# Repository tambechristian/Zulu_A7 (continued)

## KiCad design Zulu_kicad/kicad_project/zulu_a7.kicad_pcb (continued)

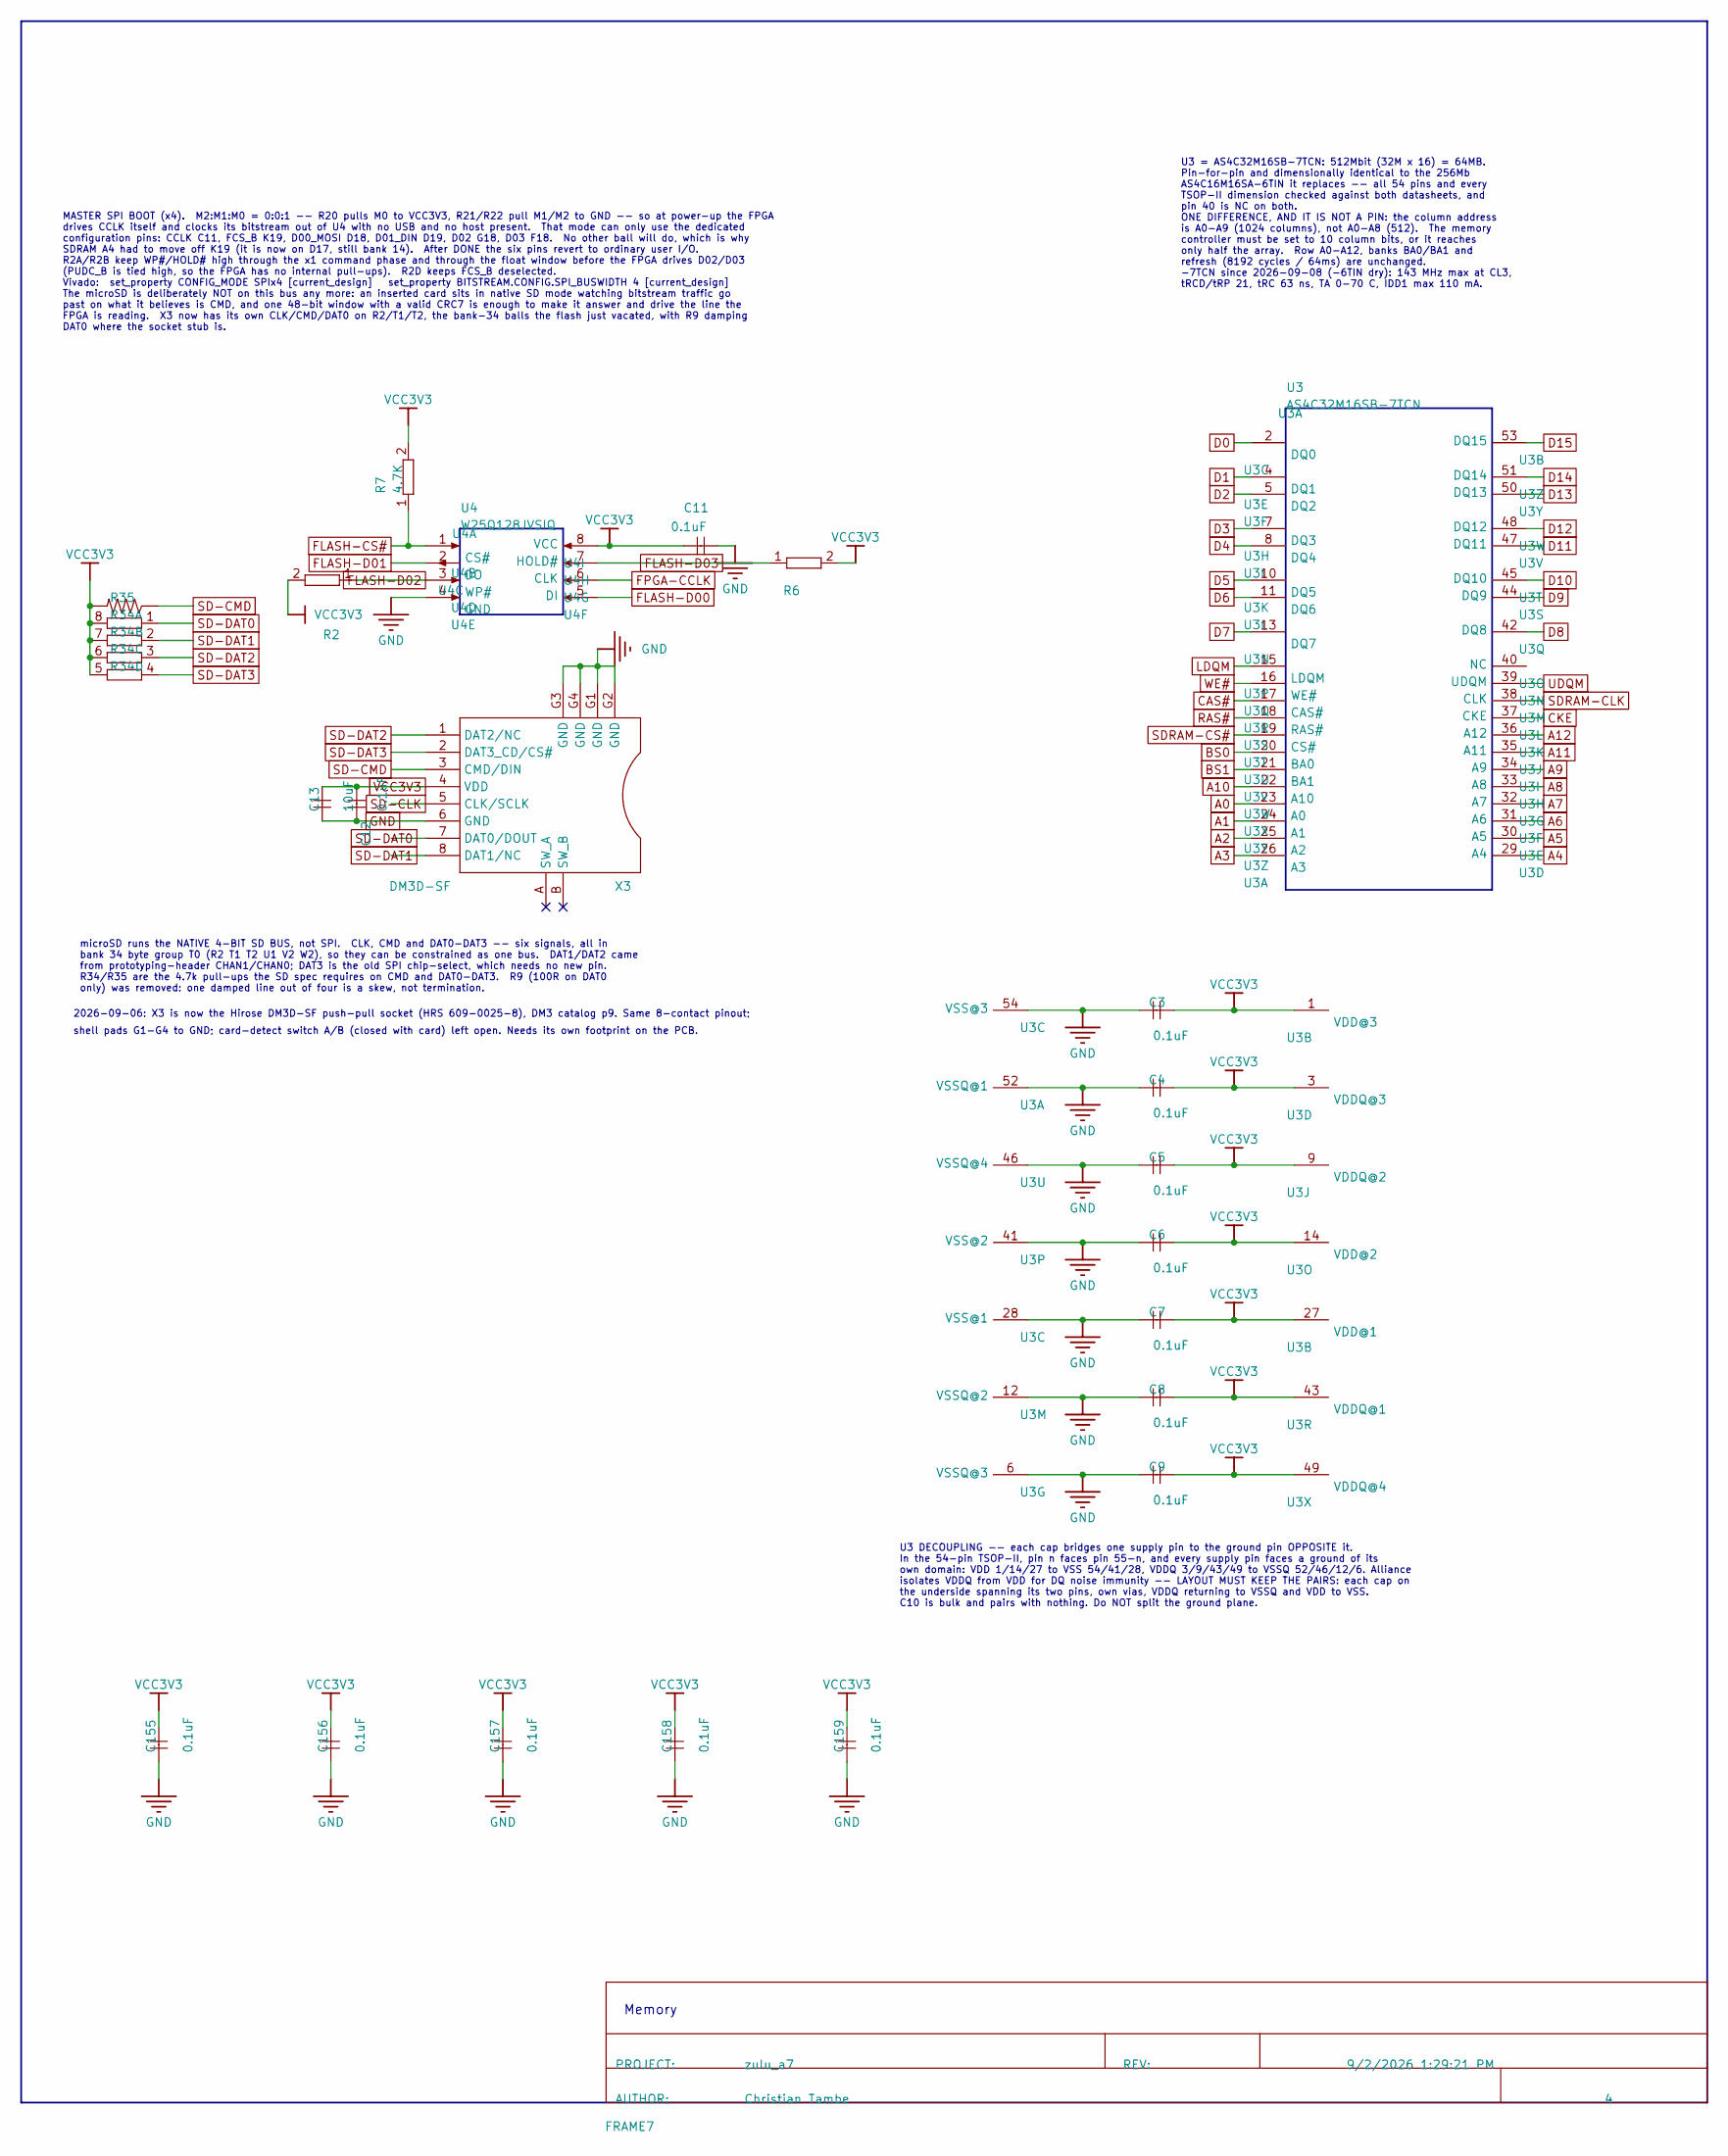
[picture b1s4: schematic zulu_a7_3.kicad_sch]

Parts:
C3, C4, C5, C6, C7, C8, C9, C11, C12: 0.1uF; C0402
C13: 10uF; C0603
C155, C156, C157, C158, C159: 0.1uF; C0201
FRAME7: DOCFIELD
R2, R6, R7: 4.7K; R0201
R34: 4.7K; 742C083; MOUSER# 774-742C083???JP; DIGIKEY# 742C083???JPCT-ND
R35: 4.7K; R0402
U3: AS4C32M16SB-7TCN; TSOPII-54
U4: W25Q128JVSIQ; SOIC-8_208MIL; PART U4; DIGIKEY# W25Q128JVSIQ-ND
X3: DM3D-SF; MOUSER# MOUSER#

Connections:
A0: U3.23; also elsewhere on the board
A1: U3.24; also elsewhere on the board
A2: U3.25; also elsewhere on the board
A3: U3.26; also elsewhere on the board
A4: U3.29; also elsewhere on the board
A5: U3.30; also elsewhere on the board
A6: U3.31; also elsewhere on the board
A7: U3.32; also elsewhere on the board
A8: U3.33; also elsewhere on the board
A9: U3.34; also elsewhere on the board
A10: U3.22; also elsewhere on the board
A11: U3.35; also elsewhere on the board
A12: U3.36; also elsewhere on the board
BS0: U3.20; also elsewhere on the board
BS1: U3.21; also elsewhere on the board
CAS#: U3.17; also elsewhere on the board
CKE: U3.37; also elsewhere on the board
D0: U3.2; also elsewhere on the board
D1: U3.4; also elsewhere on the board
D2: U3.5; also elsewhere on the board
D3: U3.7; also elsewhere on the board
D4: U3.8; also elsewhere on the board
D5: U3.10; also elsewhere on the board
D6: U3.11; also elsewhere on the board
D7: U3.13; also elsewhere on the board
D8: U3.42; also elsewhere on the board
D9: U3.44; also elsewhere on the board
D10: U3.45; also elsewhere on the board
D11: U3.47; also elsewhere on the board
D12: U3.48; also elsewhere on the board
D13: U3.50; also elsewhere on the board
D14: U3.51; also elsewhere on the board
D15: U3.53; also elsewhere on the board
FLASH-CS#: R7.1, U4.1; also elsewhere on the board
FLASH-D00: U4.5; also elsewhere on the board
FLASH-D01: U4.2; also elsewhere on the board
FLASH-D02: R2.1, U4.3; also elsewhere on the board
FLASH-D03: R6.1, U4.7; also elsewhere on the board
FPGA-CCLK: U4.6; also elsewhere on the board
GND: C3.1, C4.1, C5.1, C6.1, C7.1, C8.1, C9.1, C11.1, C12.1, C13.1, C155.1, C156.1, C157.1, C158.1, C159.1, U3.6, U3.12, U3.28, U3.41, U3.46, U3.52, U3.54, U4.4, X3.6 (GND), X3.G1 (GND), X3.G2 (GND), X3.G3 (GND), X3.G4 (GND); also elsewhere on the board
LDQM: U3.15; also elsewhere on the board
RAS#: U3.18; also elsewhere on the board
SD-CLK: X3.5 (CLK/SCLK); also elsewhere on the board
SD-CMD: R35.1, X3.3 (CMD/DIN); also elsewhere on the board
SD-DAT0: R34.1, X3.7 (DAT0/DOUT); also elsewhere on the board
SD-DAT1: R34.2 (1), X3.8 (DAT1/NC); also elsewhere on the board
SD-DAT2: R34.3 (1), X3.1 (DAT2/NC); also elsewhere on the board
SD-DAT3: R34.4 (1), X3.2 (DAT3_CD/CS#); also elsewhere on the board
SDRAM-CLK: U3.38; also elsewhere on the board
SDRAM-CS#: U3.19; also elsewhere on the board
UDQM: U3.39; also elsewhere on the board
VCC3V3: C3.2, C4.2, C5.2, C6.2, C7.2, C8.2, C9.2, C11.2, C12.2, C13.2, C155.2, C156.2, C157.2, C158.2, C159.2, R2.2, R6.2, R7.2, R34.5 (2), R34.6 (2), R34.7 (2), R34.8 (2), R35.2, U3.1, U3.3, U3.9, U3.14, U3.27, U3.43, U3.49, U4.8, X3.4 (VDD); also elsewhere on the board
WE#: U3.16; also elsewhere on the board

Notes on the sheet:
Memory
shell pads G1-G4 to GND; card-detect switch A/B (closed with card) left open. Needs its own footprint on the PCB.
2026-09-06: X3 is now the Hirose DM3D-SF push-pull socket (HRS 609-0025-8), DM3 catalog p9. Same 8-contact pinout;
MASTER SPI BOOT (x4). M2:M1:M0 = 0:0:1 -- R20 pulls M0 to VCC3V3, R21/R22 pull M1/M2 to GND -- so at power-up the FPGA drives CCLK itself and clocks its bitstream out of U4 with no USB and no host present. That mode can only use the dedicated configuration pins: CCLK C11, FCS_B K19, D00_MOSI D18, D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
U3 DECOUPLING -- each cap bridges one supply pin to the ground pin OPPOSITE it. In the 54-pin TSOP-II, pin n faces pin 55-n, and every supply pin faces a ground of its own domain: VDD 1/14/27 to VSS 54/41/28, VDDQ 3/9/43/49 to VSSQ 52/46/12/6. Alliance isolates VDDQ from VDD for DQ noise immunity -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
U3 = AS4C32M16SB-7TCN: 512Mbit (32M x 16) = 64MB. Pin-for-pin and dimensionally identical to the 256Mb AS4C16M16SA-6TIN it replaces -- all 54 pins and every TSOP-II dimension checked against both datasheets, and pin 40 is NC on both. ONE DIFFERENCE, AND IT IS NOT A PIN: the column address is A0-A9 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
microSD runs the NATIVE 4-BIT SD BUS, not SPI. CLK, CMD and DAT0-DAT3 -- six signals, all in bank 34 byte group T0 (R2 T1 T2 U1 V2 W2), so they can be constrained as one bus. DAT1/DAT2 came from prototyping-header CHAN1/CHAN0; DAT3 is the old SPI chip-select, which needs no new pin. R34/R35 are the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

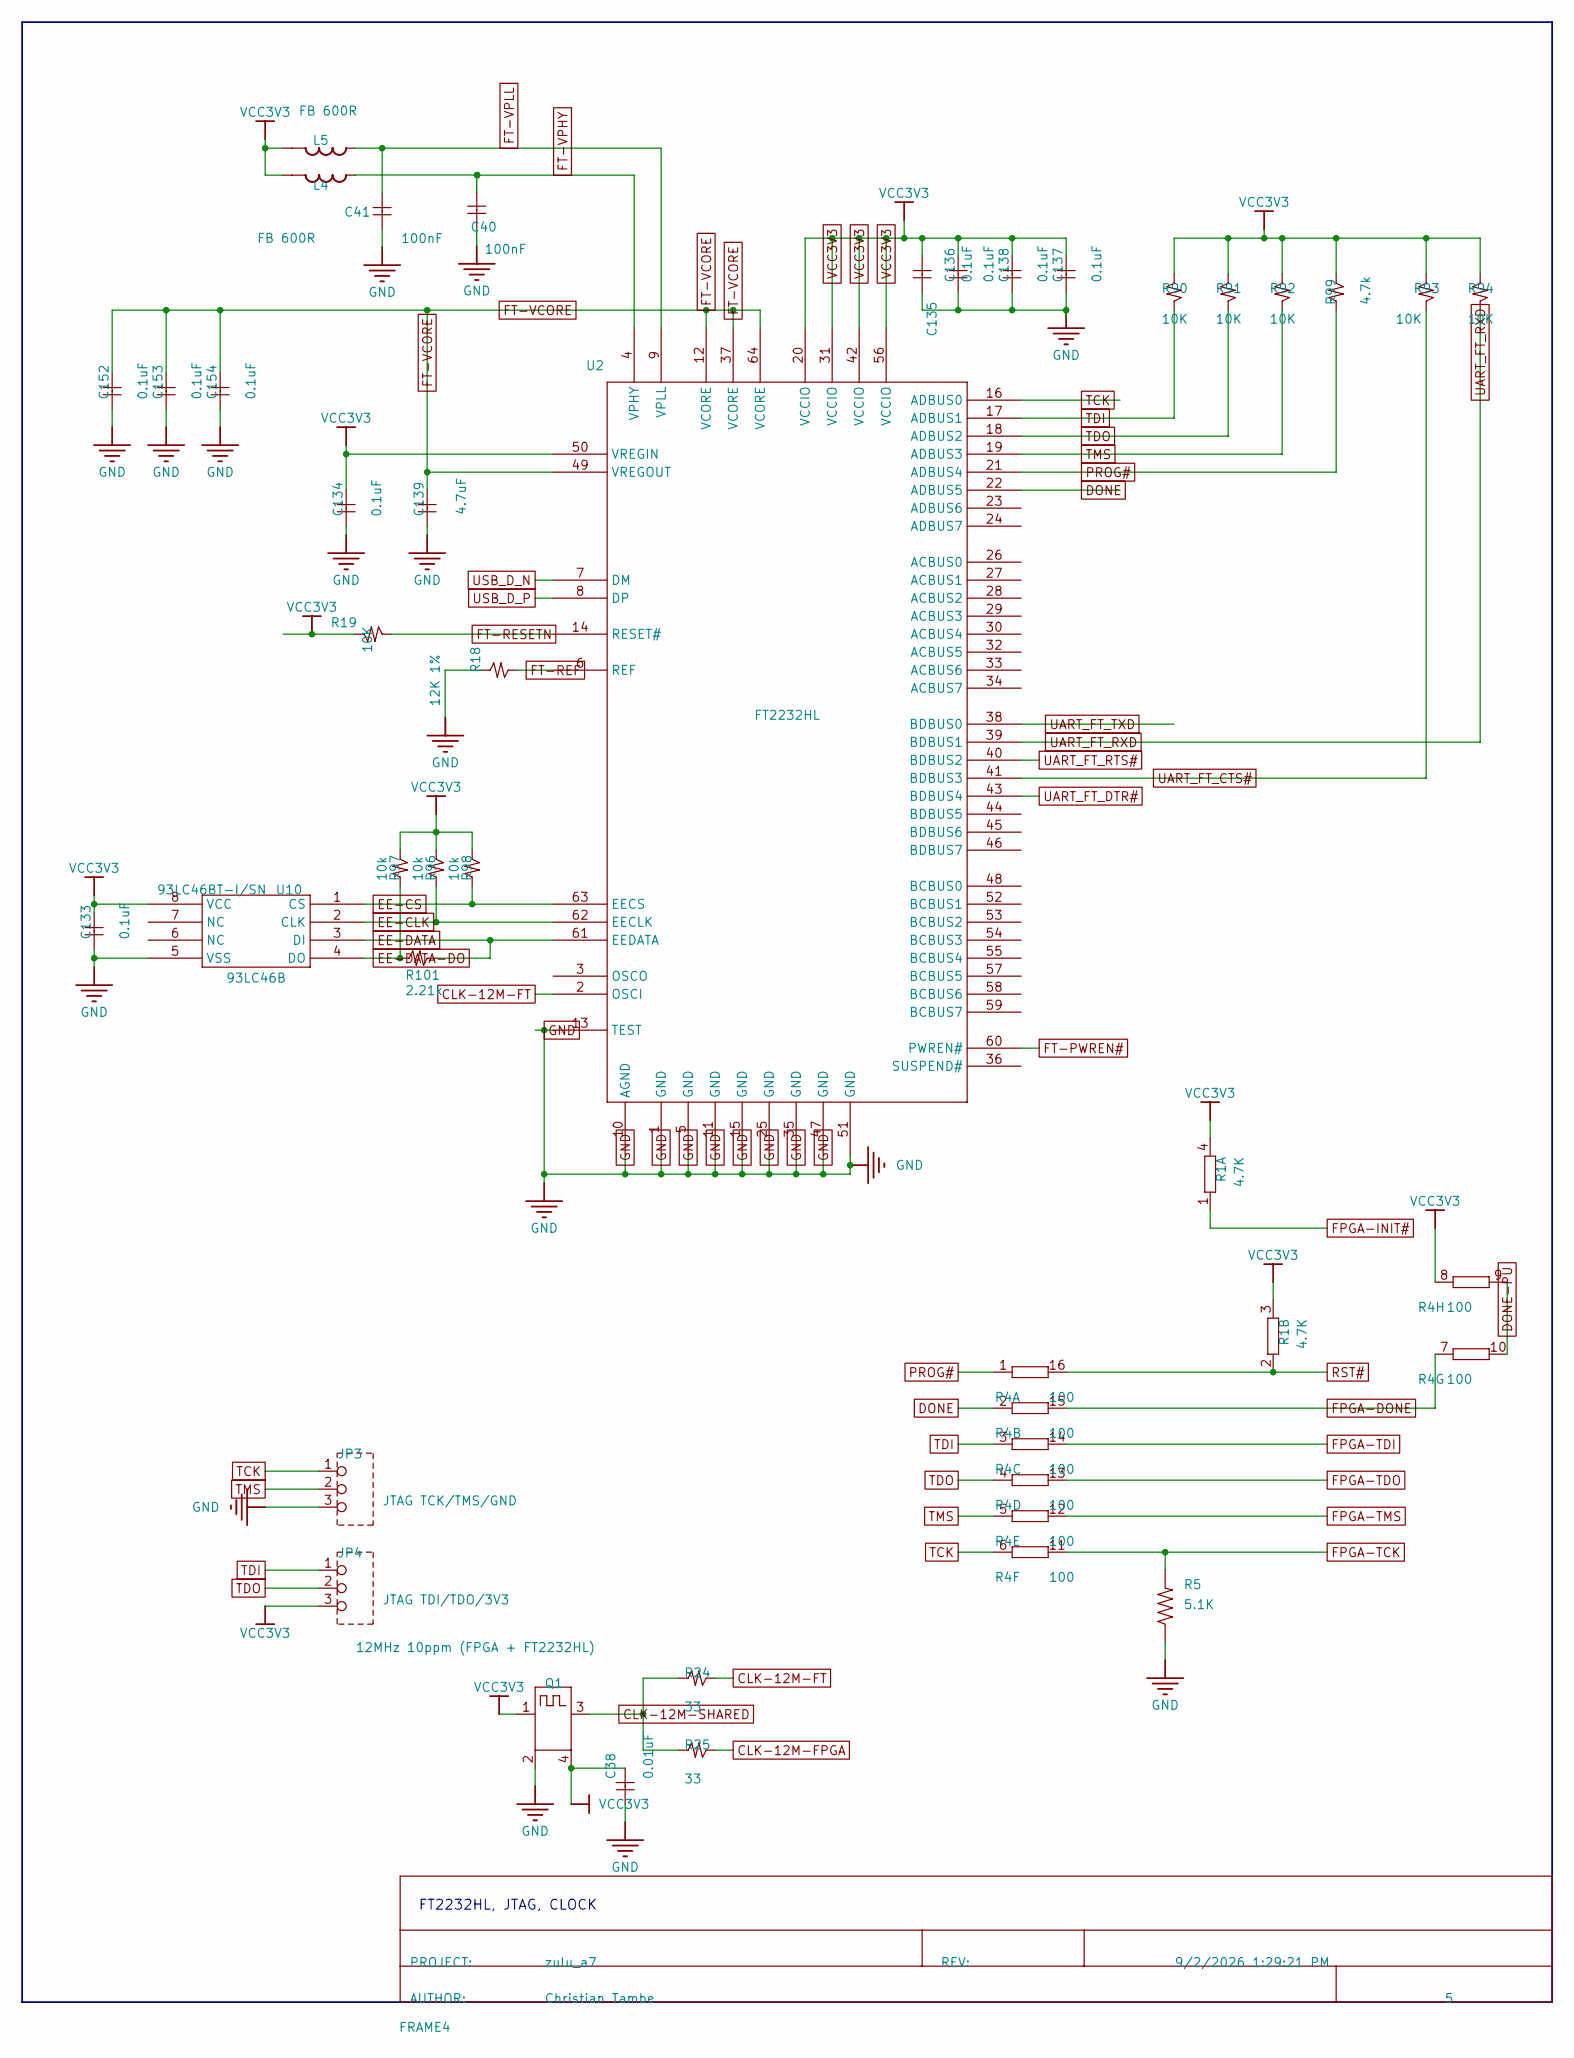
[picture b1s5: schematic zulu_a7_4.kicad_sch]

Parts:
C38: 0.01uF; C0201
C40, C41: 100nF; C0201
C133, C134, C135, C136, C137, C138, C152, C153, C154: 0.1uF; C0201
C139: 4.7uF; C0402
FRAME4: DOCFIELD
JP3: JTAG TCK/TMS/GND; 1X03-NOSILK
JP4: JTAG TDI/TDO/3V3; 1X03-NOSILK
L4, L5: FB 600R; IND0603
Q1: 12MHz 10ppm (FPGA + FT2232HL); 32X25
R1: 4.7K; 742C043
R4: 100; 742C163
R5: 5.1K; R0201; MOUSER# 301-5.1K-RC
R18: 12K 1%; R0402
R19, R90, R91, R92, R93, R94: 10K; R0201
R24, R25: 33; R0201
R96, R97, R98: 10k; R0201
R99: 4.7k; R0201
R101: 2.21k; R0201
U2: FT2232HL USB-UART/JTAG Bridge; FT2232HL-LQFP64
U10: 93LC46BT-I/SN; SPI-8_SOIC_150

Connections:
CLK-12M-FPGA: R25.2; also elsewhere on the board
CLK-12M-FT: R24.2, U2.2 (OSCI)
CLK-12M-SHARED: Q1.3, R24.1, R25.1
DONE: R4.2 (1), U2.22 (ADBUS5)
DONE-PU: R4.9 (2), R4.10 (2)
EE-CLK: R96.1, U2.62 (EECLK), U10.2 (CLK)
EE-CS: R98.1, U2.63 (EECS), U10.1 (CS)
EE-DATA: R101.2, U2.61 (EEDATA), U10.3 (DI)
EE-DATA-DO: R97.1, R101.1, U10.4 (DO)
FPGA-DONE: R4.7 (1), R4.15 (2); also elsewhere on the board
FPGA-INIT#: R1.1; also elsewhere on the board
FPGA-TCK: R4.11 (2), R5.2; also elsewhere on the board
FPGA-TDI: R4.14 (2); also elsewhere on the board
FPGA-TDO: R4.13 (2); also elsewhere on the board
FPGA-TMS: R4.12 (2); also elsewhere on the board
FT-PWREN#: U2.60 (PWREN#); also elsewhere on the board
FT-REF: R18.2, U2.6 (REF)
FT-RESETN: R19.1, U2.14 (RESET#)
FT-VCORE: C139.2, C152.2, C153.2, C154.2, U2.12 (VCORE), U2.37 (VCORE), U2.49 (VREGOUT), U2.64 (VCORE)
FT-VPHY: C40.2, L4.1, U2.4 (VPHY)
FT-VPLL: C41.2, L5.1, U2.9 (VPLL)
GND: C38.1, C40.1, C41.1, C133.1, C134.1, C135.1, C136.1, C137.1, C138.1, C139.1, C152.1, C153.1, C154.1, JP3.3, Q1.2, R5.1, R18.1, U2.1 (GND), U2.5 (GND), U2.10 (AGND), U2.11 (GND), U2.13 (TEST), U2.15 (GND), U2.25 (GND), U2.35 (GND), U2.47 (GND), U2.51 (GND), U10.5 (VSS); also elsewhere on the board
PROG#: R4.1, R99.1, U2.21 (ADBUS4)
RST#: R1.2 (1), R4.16 (2); also elsewhere on the board
TCK: JP3.1, R4.6 (1), U2.16 (ADBUS0)
TDI: JP4.1, R4.3 (1), R90.1, U2.17 (ADBUS1)
TDO: JP4.2, R4.4 (1), R91.1, U2.18 (ADBUS2)
TMS: JP3.2, R4.5 (1), R92.1, U2.19 (ADBUS3)
UART_FT_CTS#: R93.1, U2.41 (BDBUS3); also elsewhere on the board
UART_FT_DTR#: U2.43 (BDBUS4); also elsewhere on the board
UART_FT_RTS#: U2.40 (BDBUS2); also elsewhere on the board
UART_FT_RXD: R94.1, U2.39 (BDBUS1); also elsewhere on the board
UART_FT_TXD: U2.38 (BDBUS0); also elsewhere on the board
USB_D_N: U2.7 (DM); also elsewhere on the board
USB_D_P: U2.8 (DP); also elsewhere on the board
VCC3V3: C38.2, C133.2, C134.2, C135.2, C136.2, C137.2, C138.2, JP4.3, L4.2, L5.2, Q1.1, Q1.4, R1.3 (2), R1.4 (2), R4.8 (1), R19.2, R90.2, R91.2, R92.2, R93.2, R94.2, R96.2, R97.2, R98.2, R99.2, U2.20 (VCCIO), U2.31 (VCCIO), U2.42 (VCCIO), U2.50 (VREGIN), U2.56 (VCCIO), U10.8 (VCC); also elsewhere on the board

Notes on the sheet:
FT2232HL, JTAG, CLOCK

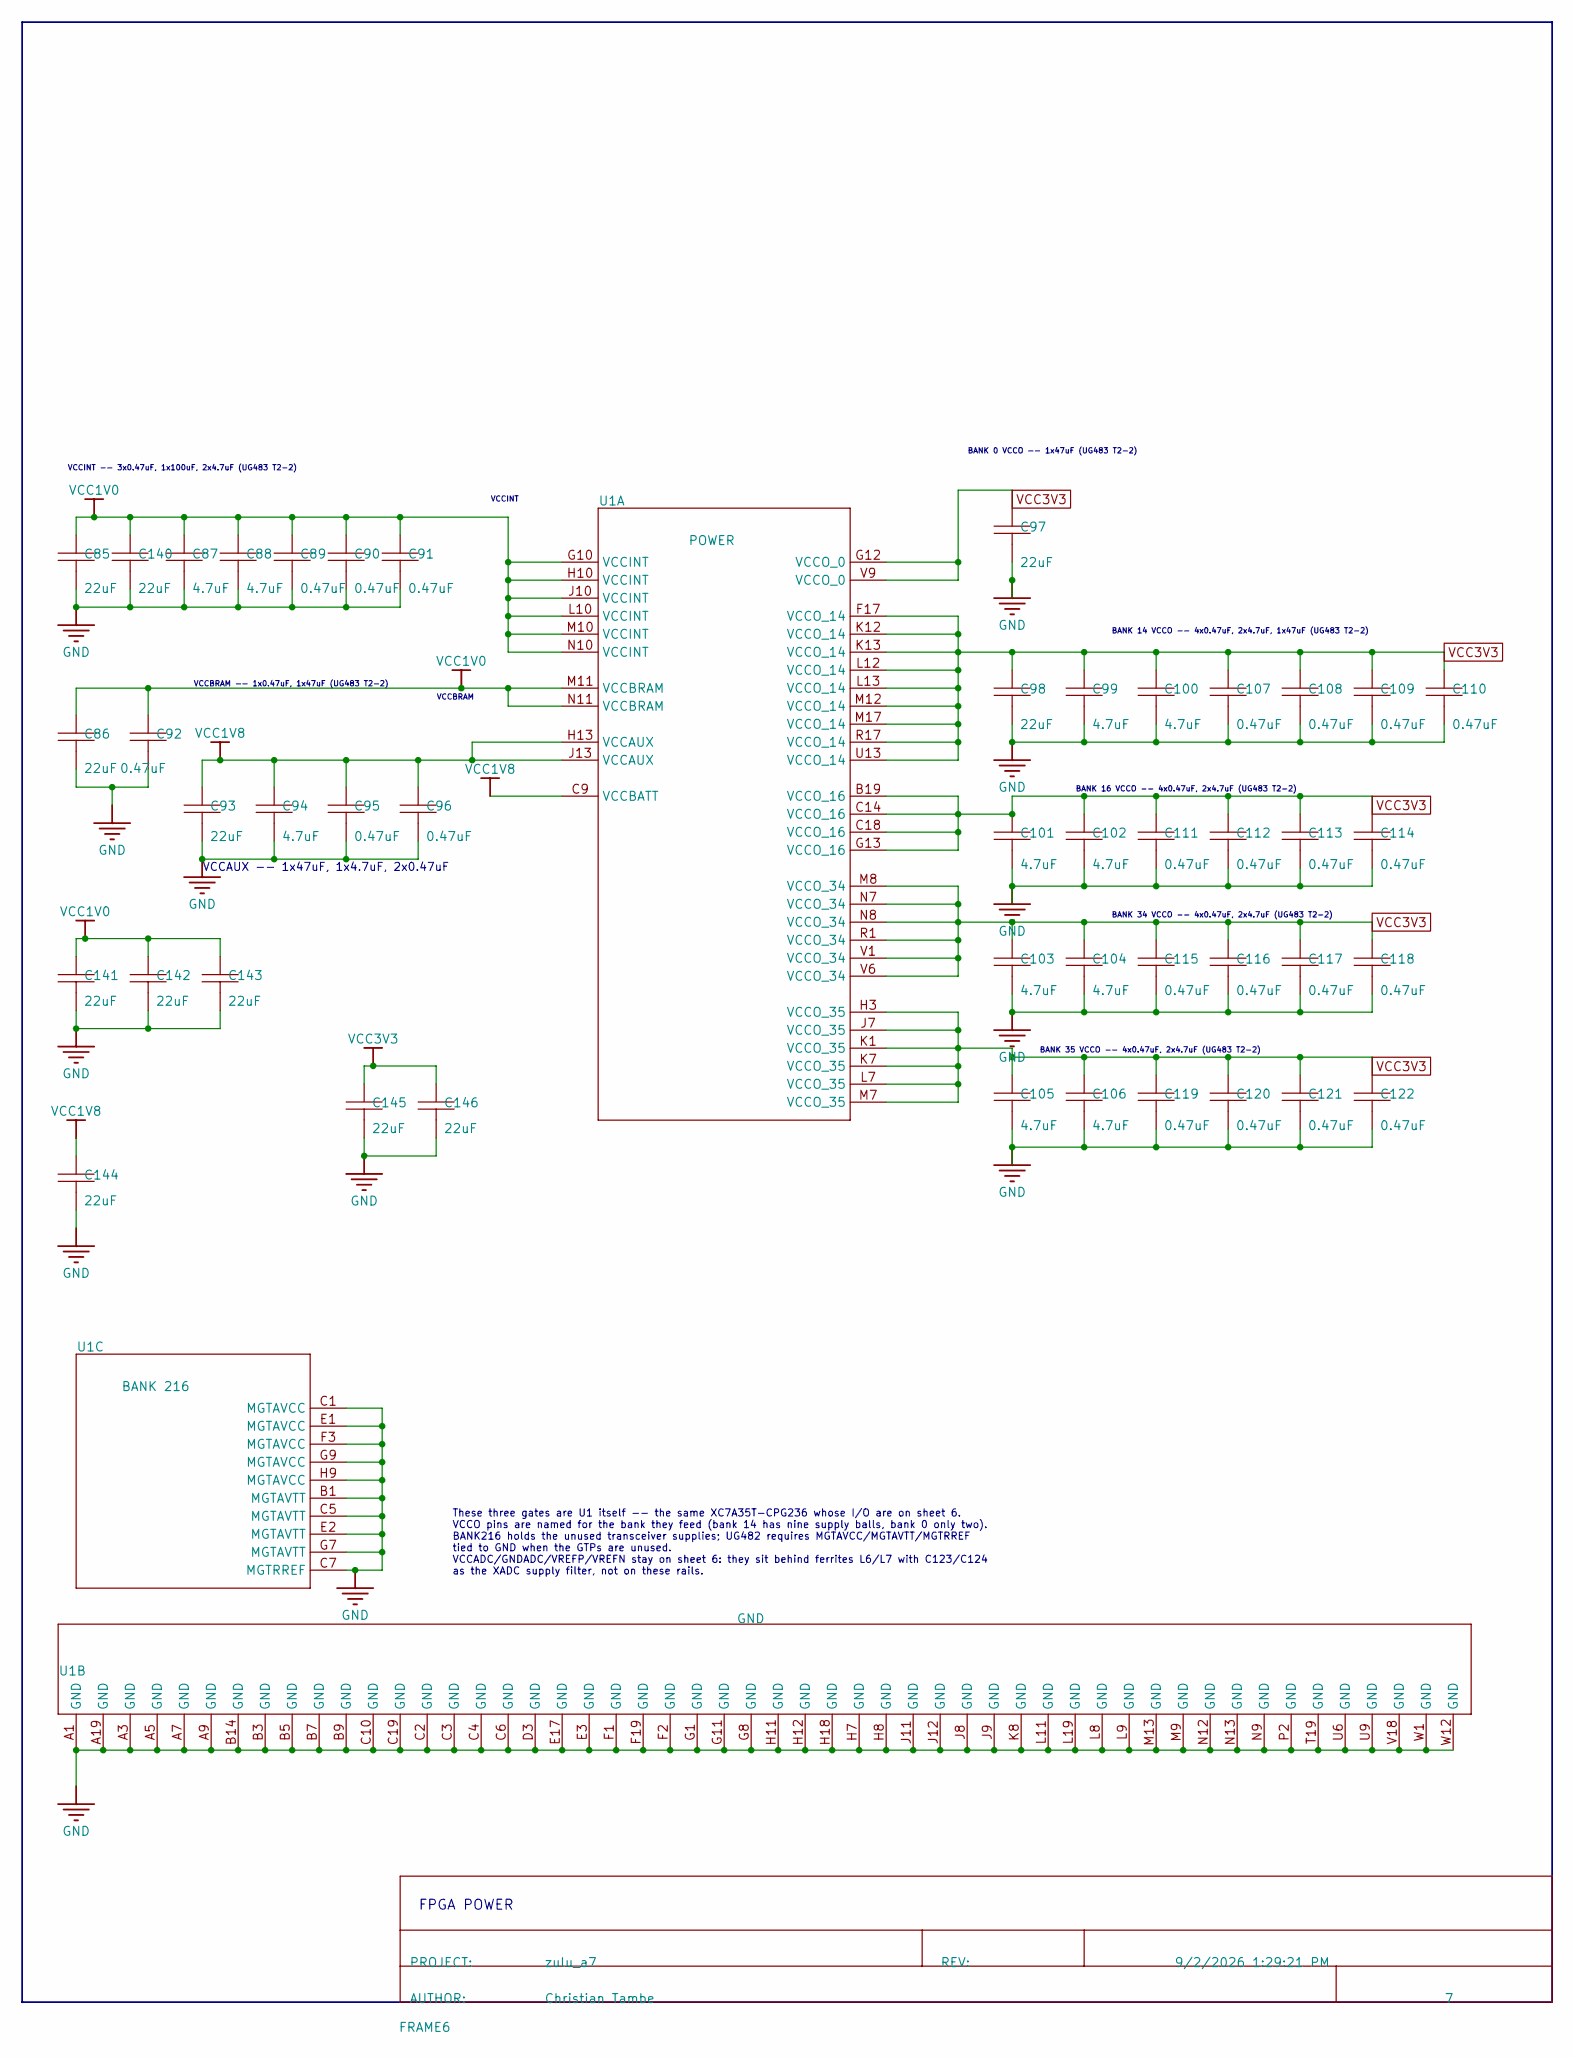
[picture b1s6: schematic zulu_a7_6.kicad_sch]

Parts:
C85, C86, C93, C97, C98, C140, C141, C142, C143, C144, C145, C146: 22uF; C0805
C87, C88, C94, C99, C100, C101, C102, C103, C104, C105, C106: 4.7uF; C0603
C89, C90, C91, C92, C95, C96, C107, C108, C109, C110, C111, C112, C113, C114, C115, C116, C117, C118, C119, C120, C121, C122: 0.47uF; C0201
FRAME6: DOCFIELD
U1: XC7A35T-2CPG236I; XC7A35T-CPG236

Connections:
A0: U1.U2 (1); also elsewhere on the board
A1: U1.T3 (1); also elsewhere on the board
A2: U1.T2 (1); also elsewhere on the board
A3: U1.T1 (1); also elsewhere on the board
A4: U1.R3 (1); also elsewhere on the board
A5: U1.R2 (1); also elsewhere on the board
A6: U1.P3 (1); also elsewhere on the board
A7: U1.P1 (1); also elsewhere on the board
A8: U1.N3 (1); also elsewhere on the board
A9: U1.N2 (1); also elsewhere on the board
A10: U1.U3 (1); also elsewhere on the board
A11: U1.N1 (1); also elsewhere on the board
A12: U1.M3 (1); also elsewhere on the board
AIN15_N: U1.G2 (1); also elsewhere on the board
AIN15_P: U1.G3 (1); also elsewhere on the board
AIN16_N: U1.J2 (1); also elsewhere on the board
AIN16_P: U1.H2 (1); also elsewhere on the board
BS0: U1.V2 (1); also elsewhere on the board
BS1: U1.U1 (1); also elsewhere on the board
BTN: U1.N19 (1); also elsewhere on the board
CAS#: U1.W3 (1); also elsewhere on the board
CFG-M0: U1.V12 (1); also elsewhere on the board
CFG-M1: U1.W11 (1); also elsewhere on the board
CFG-M2: U1.U10 (1); also elsewhere on the board
CHAN0: U1.B18 (1); also elsewhere on the board
CHAN1: U1.A18 (1); also elsewhere on the board
CHAN2: U1.B17 (1); also elsewhere on the board
CHAN3: U1.A17 (1); also elsewhere on the board
CHAN4: U1.C16 (1); also elsewhere on the board
CHAN5: U1.D17 (1); also elsewhere on the board
CHAN6: U1.H17 (1); also elsewhere on the board
CHAN7: U1.G17 (1); also elsewhere on the board
CHAN8: U1.J18 (1); also elsewhere on the board
CHAN9: U1.J17 (1); also elsewhere on the board
CHAN10: U1.J19 (1); also elsewhere on the board
CHAN11: U1.K18 (1); also elsewhere on the board
CHAN12: U1.E19 (1); also elsewhere on the board
CHAN13: U1.H19 (1); also elsewhere on the board
CHAN14: U1.W17 (1); also elsewhere on the board
CHAN15: U1.V17 (1); also elsewhere on the board
CHAN16: U1.W16 (1); also elsewhere on the board
CHAN17: U1.U16 (1); also elsewhere on the board
CHAN18: U1.V16 (1); also elsewhere on the board
CHAN19: U1.W15 (1); also elsewhere on the board
CHAN20: U1.V15 (1); also elsewhere on the board
CHAN21: U1.U15 (1); also elsewhere on the board
CHAN22: U1.W14 (1); also elsewhere on the board
CHAN23: U1.V14 (1); also elsewhere on the board
CHAN24: U1.U14 (1); also elsewhere on the board
CHAN25: U1.W13 (1); also elsewhere on the board
CHAN26: U1.V13 (1); also elsewhere on the board
CHAN27: U1.T18 (1); also elsewhere on the board
CHAN28: U1.T17 (1); also elsewhere on the board
CHAN-CLK: U1.P18 (1); also elsewhere on the board
CKE: U1.M2 (1); also elsewhere on the board
CLK-12M-FPGA: U1.L17 (1); also elsewhere on the board
D0: U1.V8 (1); also elsewhere on the board
D1: U1.V7 (1); also elsewhere on the board
D2: U1.W7 (1); also elsewhere on the board
D3: U1.W6 (1); also elsewhere on the board
D4: U1.U5 (1); also elsewhere on the board
D5: U1.W5 (1); also elsewhere on the board
D6: U1.V5 (1); also elsewhere on the board
D7: U1.U4 (1); also elsewhere on the board
D8: U1.L1 (1); also elsewhere on the board
D9: U1.K3 (1); also elsewhere on the board
D10: U1.K2 (1); also elsewhere on the board
D11: U1.J1 (1); also elsewhere on the board
D12: U1.J3 (1); also elsewhere on the board
D13: U1.H1 (1); also elsewhere on the board
D14: U1.A14 (1); also elsewhere on the board
D15: U1.A15 (1); also elsewhere on the board
FLASH-CS#: U1.K19 (1); also elsewhere on the board
FLASH-D00: U1.D18 (1); also elsewhere on the board
FLASH-D01: U1.D19 (1); also elsewhere on the board
FLASH-D02: U1.G18 (1); also elsewhere on the board
FLASH-D03: U1.F18 (1); also elsewhere on the board
FPGA-CCLK: U1.C11 (1); also elsewhere on the board
FPGA-DONE: U1.U12 (1); also elsewhere on the board
FPGA-INIT#: U1.U11 (1); also elsewhere on the board
FPGA-TCK: U1.C8 (1); also elsewhere on the board
FPGA-TDI: U1.W10 (1); also elsewhere on the board
FPGA-TDO: U1.W8 (1); also elsewhere on the board
FPGA-TMS: U1.W9 (1); also elsewhere on the board
FT-PWREN#: U1.P19 (1); also elsewhere on the board
GND: C85.2, C86.2, C87.2, C88.2, C89.2, C90.2, C91.2, C92.2, C93.2, C94.2, C95.2, C96.2, C97.2, C98.2, C99.2, C100.2, C101.2, C102.2, C103.2, C104.2, C105.2, C106.2, C107.2, C108.2, C109.2, C110.2, C111.2, C112.2, C113.2, C114.2, C115.2, C116.2, C117.2, C118.2, C119.2, C120.2, C121.2, C122.2, C140.2, C141.2, C142.2, C143.2, C144.2, C145.2, C146.2, U1.A1 (GND), U1.A3 (GND), U1.A4 (1), U1.A5 (GND), U1.A6 (1), U1.A7 (GND), U1.A9 (GND), U1.A11 (1), U1.A19 (GND), U1.B1 (MGTAVTT), U1.B3 (GND), U1.B4 (1), U1.B5 (GND), U1.B6 (1), U1.B7 (GND), U1.B9 (GND), U1.B11 (1), U1.B14 (GND), U1.C1 (MGTAVCC), U1.C2 (GND), U1.C3 (GND), U1.C4 (GND), U1.C5 (MGTAVTT), U1.C6 (GND), U1.C7 (MGTRREF), U1.C10 (GND), U1.C19 (GND), U1.D3 (GND), U1.E1 (MGTAVCC), U1.E2 (MGTAVTT), U1.E3 (GND), U1.E17 (GND), U1.F1 (GND), U1.F2 (GND), U1.F3 (MGTAVCC), U1.F19 (GND), U1.G1 (GND), U1.G7 (MGTAVTT), U1.G8 (GND), U1.G9 (MGTAVCC), U1.G11 (GND), U1.H7 (GND), U1.H8 (GND), U1.H9 (MGTAVCC), U1.H11 (GND), U1.H12 (GND), U1.H18 (GND), U1.J8 (GND), U1.J9 (GND), U1.J11 (GND), U1.J12 (GND), U1.K8 (GND), U1.L8 (GND), U1.L9 (GND), U1.L11 (GND), U1.L19 (GND), U1.M9 (GND), U1.M13 (GND), U1.N9 (GND), U1.N12 (GND), U1.N13 (GND), U1.P2 (GND), U1.T19 (GND), U1.U6 (GND), U1.U9 (GND), U1.V18 (GND), U1.W1 (GND), U1.W12 (GND); also elsewhere on the board
GNDADC: U1.A12 (1), U1.A13 (1), U1.B12 (1), U1.B13 (1), U1.C12 (1); also elsewhere on the board
JA1: U1.U18 (1); also elsewhere on the board
JA2: U1.U19 (1); also elsewhere on the board
JA3: U1.W18 (1); also elsewhere on the board
JA4: U1.C17 (1); also elsewhere on the board
JA7: U1.R19 (1); also elsewhere on the board
JA8: U1.W19 (1); also elsewhere on the board
JA9: U1.V19 (1); also elsewhere on the board
JA10: U1.U17 (1); also elsewhere on the board
LDQM: U1.W4 (1); also elsewhere on the board
LED0_B: U1.N17 (1); also elsewhere on the board
LED0_G: U1.R18 (1); also elsewhere on the board
LED0_R: U1.P17 (1); also elsewhere on the board
LED1: U1.N18 (1); also elsewhere on the board
LED2: U1.M19 (1); also elsewhere on the board
PUDC_B: U1.E18 (1); also elsewhere on the board
RAS#: U1.V3 (1); also elsewhere on the board
RST#: U1.V10 (1); also elsewhere on the board
SD-CLK: U1.U8 (1); also elsewhere on the board
SD-CMD: U1.U7 (1); also elsewhere on the board
SD-DAT0: U1.C15 (1); also elsewhere on the board
SD-DAT1: U1.B15 (1); also elsewhere on the board
SD-DAT2: U1.L3 (1); also elsewhere on the board
SD-DAT3: U1.A16 (1); also elsewhere on the board
SDRAM-CLK: U1.M1 (1); also elsewhere on the board
SDRAM-CS#: U1.W2 (1); also elsewhere on the board
UART_FT_CTS#: U1.B16 (1); also elsewhere on the board
UART_FT_DTR#: U1.M18 (1); also elsewhere on the board
UART_FT_RTS#: U1.L18 (1); also elsewhere on the board
UART_FT_RXD: U1.G19 (1); also elsewhere on the board
UART_FT_TXD: U1.K17 (1); also elsewhere on the board
UDQM: U1.L2 (1); also elsewhere on the board
VCC1V0: C85.1, C86.1, C87.1, C88.1, C89.1, C90.1, C91.1, C92.1, C140.1, C141.1, C142.1, C143.1, U1.G10 (VCCINT), U1.H10 (VCCINT), U1.J10 (VCCINT), U1.L10 (VCCINT), U1.M10 (VCCINT), U1.M11 (VCCBRAM), U1.N10 (VCCINT), U1.N11 (VCCBRAM); also elsewhere on the board
VCC1V8: C93.1, C94.1, C95.1, C96.1, C144.1, U1.C9 (VCCBATT), U1.H13 (VCCAUX), U1.J13 (VCCAUX); also elsewhere on the board
VCC3V3: C97.1, C98.1, C99.1, C100.1, C101.1, C102.1, C103.1, C104.1, C105.1, C106.1, C107.1, C108.1, C109.1, C110.1, C111.1, C112.1, C113.1, C114.1, C115.1, C116.1, C117.1, C118.1, C119.1, C120.1, C121.1, C122.1, C145.1, C146.1, U1.B19 (VCCO_16), U1.C14 (VCCO_16), U1.C18 (VCCO_16), U1.F17 (VCCO_14), U1.G12 (VCCO_0), U1.G13 (VCCO_16), U1.H3 (VCCO_35), U1.J7 (VCCO_35), U1.K1 (VCCO_35), U1.K7 (VCCO_35), U1.K12 (VCCO_14), U1.K13 (VCCO_14), U1.L7 (VCCO_35), U1.L12 (VCCO_14), U1.L13 (VCCO_14), U1.M7 (VCCO_35), U1.M8 (VCCO_34), U1.M12 (VCCO_14), U1.M17 (VCCO_14), U1.N7 (VCCO_34), U1.N8 (VCCO_34), U1.R1 (VCCO_34), U1.R17 (VCCO_14), U1.U13 (VCCO_14), U1.V1 (VCCO_34), U1.V6 (VCCO_34), U1.V9 (VCCO_0), U1.V11 (1); also elsewhere on the board
VCCADC: U1.C13 (1); also elsewhere on the board
WE#: U1.V4 (1); also elsewhere on the board

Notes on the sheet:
BANK 0 VCCO -- 1x47uF (UG483 T2-2)
BANK 16 VCCO -- 4x0.47uF, 2x4.7uF (UG483 T2-2)
VCCINT
VCCINT -- 3x0.47uF, 1x100uF, 2x4.7uF (UG483 T2-2)
BANK 35 VCCO -- 4x0.47uF, 2x4.7uF (UG483 T2-2)
VCCAUX -- 1x47uF, 1x4.7uF, 2x0.47uF
VCCBRAM
BANK 34 VCCO -- 4x0.47uF, 2x4.7uF (UG483 T2-2)
FPGA POWER
VCCBRAM -- 1x0.47uF, 1x47uF (UG483 T2-2)
BANK 14 VCCO -- 4x0.47uF, 2x4.7uF, 1x47uF (UG483 T2-2)
These three gates are U1 itself -- the same XC7A35T-CPG236 whose I/O are on sheet 6. VCCO pins are named for the bank they feed (bank 14 has nine supply balls, bank 0 only two). BANK216 holds the unused transceiver supplies; UG482 requires MGTAVCC/MGTAVTT/MGTRREF tied to GND when the GTPs are unuse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
